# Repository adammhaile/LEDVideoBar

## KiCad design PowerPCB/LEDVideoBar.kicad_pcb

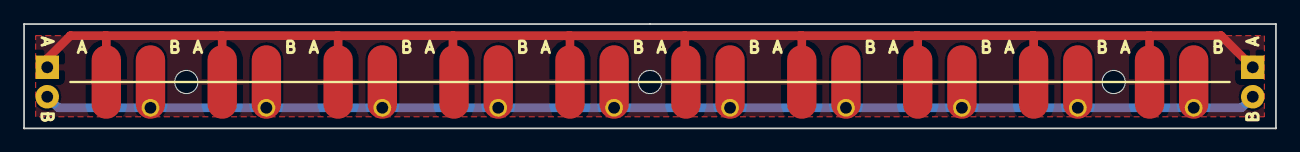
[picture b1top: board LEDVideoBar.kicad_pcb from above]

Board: 2 copper layers, 108.0 x 9.0 mm, 12 parts (0 on the bottom side), 2 nets.

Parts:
I1, I2: Strip; 2Pin
P1, P2, P3, P4, P5, P6, P7, P8, P9, P10: Strip; LEDStripSMD

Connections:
unnamed: I1.1, I2.1, P1.1, P2.1, P3.1, P4.1, P5.1, P6.1, P7.1, P8.1, P9.1, P10.1
unnamed: I1.2, I2.2, P1.2, P2.2, P3.2, P4.2, P5.2, P6.2, P7.2, P8.2, P9.2, P10.2

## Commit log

2016-05-14 :lollipop: Added .gitattributes
2016-05-15 init
